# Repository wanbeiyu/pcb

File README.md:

# PCB

## 3rd_party libraries

<table>
<tr><th>Part Number</th><th>Download Link</th></tr>
<tr><td>2171790001</td><td>

[ul_2171790001.zip](https://app.ultralibrarian.com/details/b6ea985d-a10c-11eb-9033-0a34d6323d74/Molex-Connector-Corporation/2171790001)

<dl>
<dt>Symbol</dt><dd>Normal View, 2171790001 1</dd>
<dt>Footprint</dt><dd>Basic View, 2171790001_MOL</dd>
<dt>Select Your CAD Format</dt><dd>3D CAD Model: STEP, KiCAD v6+</dd>
<dt>Symbol Pin Ordering</dt><dd>Sequential</dd>
<dt>Footprint Units</dt><dd>English (mil)</dd>
</dl>

フットプリントは作り直した。

</td></tr>
<tr><td>AD8403ARUZ1-REEL</td><td>

[LIB_AD8403ARUZ1-REEL.zip](https://componentsearchengine.com/part-view/AD8403ARUZ1-REEL/Analog%20Devices)

</td></tr>
<tr><td>ADG801BRTZ-REEL7</td><td>

[LIB_ADG801BRTZ-REEL7.zip](https://componentsearchengine.com/part-view/ADG801BRTZ-REEL7/Analog%20Devices)

</td></tr>
<tr><td>AWSCR-12.00CELA-C10-T3</td><td>

C33なら存在する。シンボルのプロパティから「値」「Manufacturer_Part_Number」を編集し、「データシート」「説明」「Mouser Part Number」「Mouser Price/Stock」「Arrow Part Number」「Arrow Price/Stock」の内容を削除の上、PCBA時にC10を指定する。

[LIB_AWSCR-12.00CELA-C33-T3.zip](https://componentsearchengine.com/part-view/AWSCR-12.00CELA-C33-T3/ABRACON)

</td></tr>
<tr><td>DS4424N+T&R</td><td>

[LIB_DS4424N+T&R.zip](https://componentsearchengine.com/part-view/DS4424N%2BT%26R/Analog%20Devices)

</td></tr>
<tr><td>MCP659-E_ML</td><td>

[LIB_MCP659-E_ML.zip](https://componentsearchengine.com/part-view/MCP659-E%2FML/Microchip)

</td></tr>
<tr><td>NCP167AMX330TBG</td><td>

[ul_NCP167AMX330TBG.zip](https://app.ultralibrarian.com/details/5d94e4bf-e68c-11ea-b55a-0a34d6323d74/onsemi/NCP167AMX330TBG)

<dl>
<dt>Symbol</dt><dd>Normal View, NCP167AMX330TBG 1</dd>
<dt>Footprint</dt><dd>Basic View, XDFN4_1X1_711AJ_ONS</dd>
<dt>Select Your CAD Format</dt><dd>KiCAD v6+</dd>
<dt>Symbol Pin Ordering</dt><dd>Sequential</dd>
<dt>Footprint Units</dt><dd>English (mil)</dd>
</dl>
</td></tr>
<tr><td>SK6805-EC15</td><td>

[LIB_SK6805-EC15.zip](https://componentsearchengine.com/part-view/SK6805-EC15/Shenzhen%20Normand%20Electronic)

</td></tr>
<tr><td>TC42X-2-102E</td><td>

[LIB_TC42X-2-102E.zip](https://componentsearchengine.com/part-view/TC42X-2-102E/Bourns)

</td></tr>
<tr><td>W25Q16JVUXIQ</td><td>

[LIB_W25Q16JVUXIQ.zip](https://componentsearchengine.com/part-view/W25Q16JVUXIQ/Winbond)

</td></tr>
<tr><td>XCL103D503CR-G</td><td>

[LIB_XCL103D503CR-G.zip](https://componentsearchengine.com/part-view/XCL103D503CR-G/Torex)

</td></tr>
</table>

## 部品選定メモ

### 電源

New 3DS LLには5V以上の電源を引き出せるTPはない（電源接続時4.38V、バッテリー駆動時3.92V、消耗時は3.1V程度まで低下）。5Vに昇圧→3.3Vに降圧する。

特にコイル一体型のICが実装面積が小さくなる。XCL103のI<sub>LIM</sub>で十分と判断した。

<table>
<tr>
<th>品番</th>
<th>詳細</th>
</tr>
<tr>
<td>XCL103D503CR-G</td>
<td>

- PWM/PFM自動切替制御
- Complete Output Disconnect
- Output Voltage: 5.0V
- I<sub>LIM</sub>: 1.3A

</td>
</tr>
<tr>
<td>XCL105A501H2-G</td>
<td>

- PWM/PFM制御
- Complete Output Disconnect
  - A・Dから選択で、Aしか在庫がない<br>https://www.digikey.jp/short/0qb0394h<br>https://mou.sr/4bJGSOZ
- Output Voltage: 5.0V
- I<sub>LIM</sub>: 2.42A

</td>
</tr>
</table>

以前はRaspberry Pi Debug Probeを参考に[AP2112K-3.3TRG1](https://www.digikey.jp/ja/products/detail/diodes-incorporated/AP2112K-3-3TRG1/4470746)を使用していた。

| 機能                     | 値         |
| ------------------------ | ---------- |
| 出力構成                 | ポジティブ |
| 出力タイプ               | 固定       |
| 電圧 - 出力（最小/固定） | 3.3V       |
| 電流 - 出力              | 600mA      |

600mA以上出ていればどれでもよさそうだ。[NCP167AMX330TBG](https://www.digikey.jp/ja/products/detail/onsemi/NCP167AMX330TBG/9169759)が十分小さい。

### 発振回路

[AEL X12M000000S096](https://abracon.com/datasheets/AEL-Crystals/PN/X12M000000S096.pdf)が元の水晶[^1]。

[^1]: https://forums.raspberrypi.com/viewtopic.php?t=349741

- 12MHz
- ESR：50Ωに寄せる
- 内蔵コンデンサ
- セラミックタイプ

[検索結果](https://www.digikey.jp/short/p5qp35qr)

Operating Temperature（`CELA`は85度まで、`CELB`は125度まで）、静電容量（33pF／10pF）を選択する。以前の設計では10pFを用いたので、今回も10pF+1kΩ抵抗で使用する。

[AWSCR-12.00CELA-C10-T3](https://www.digikey.jp/short/t2mnvzrp)

## フルカラーLED

いわゆるNeoPixel、WS2812BとSK6812（12mA：たぶんより明るい）/SK6805（5mA）は同じものらしい[^2]。前者がオリジナル、後者がクローン。

[^2]: https://romly.com/blog/neopixel_variation/

SK6805-EC15が1.5mm角。

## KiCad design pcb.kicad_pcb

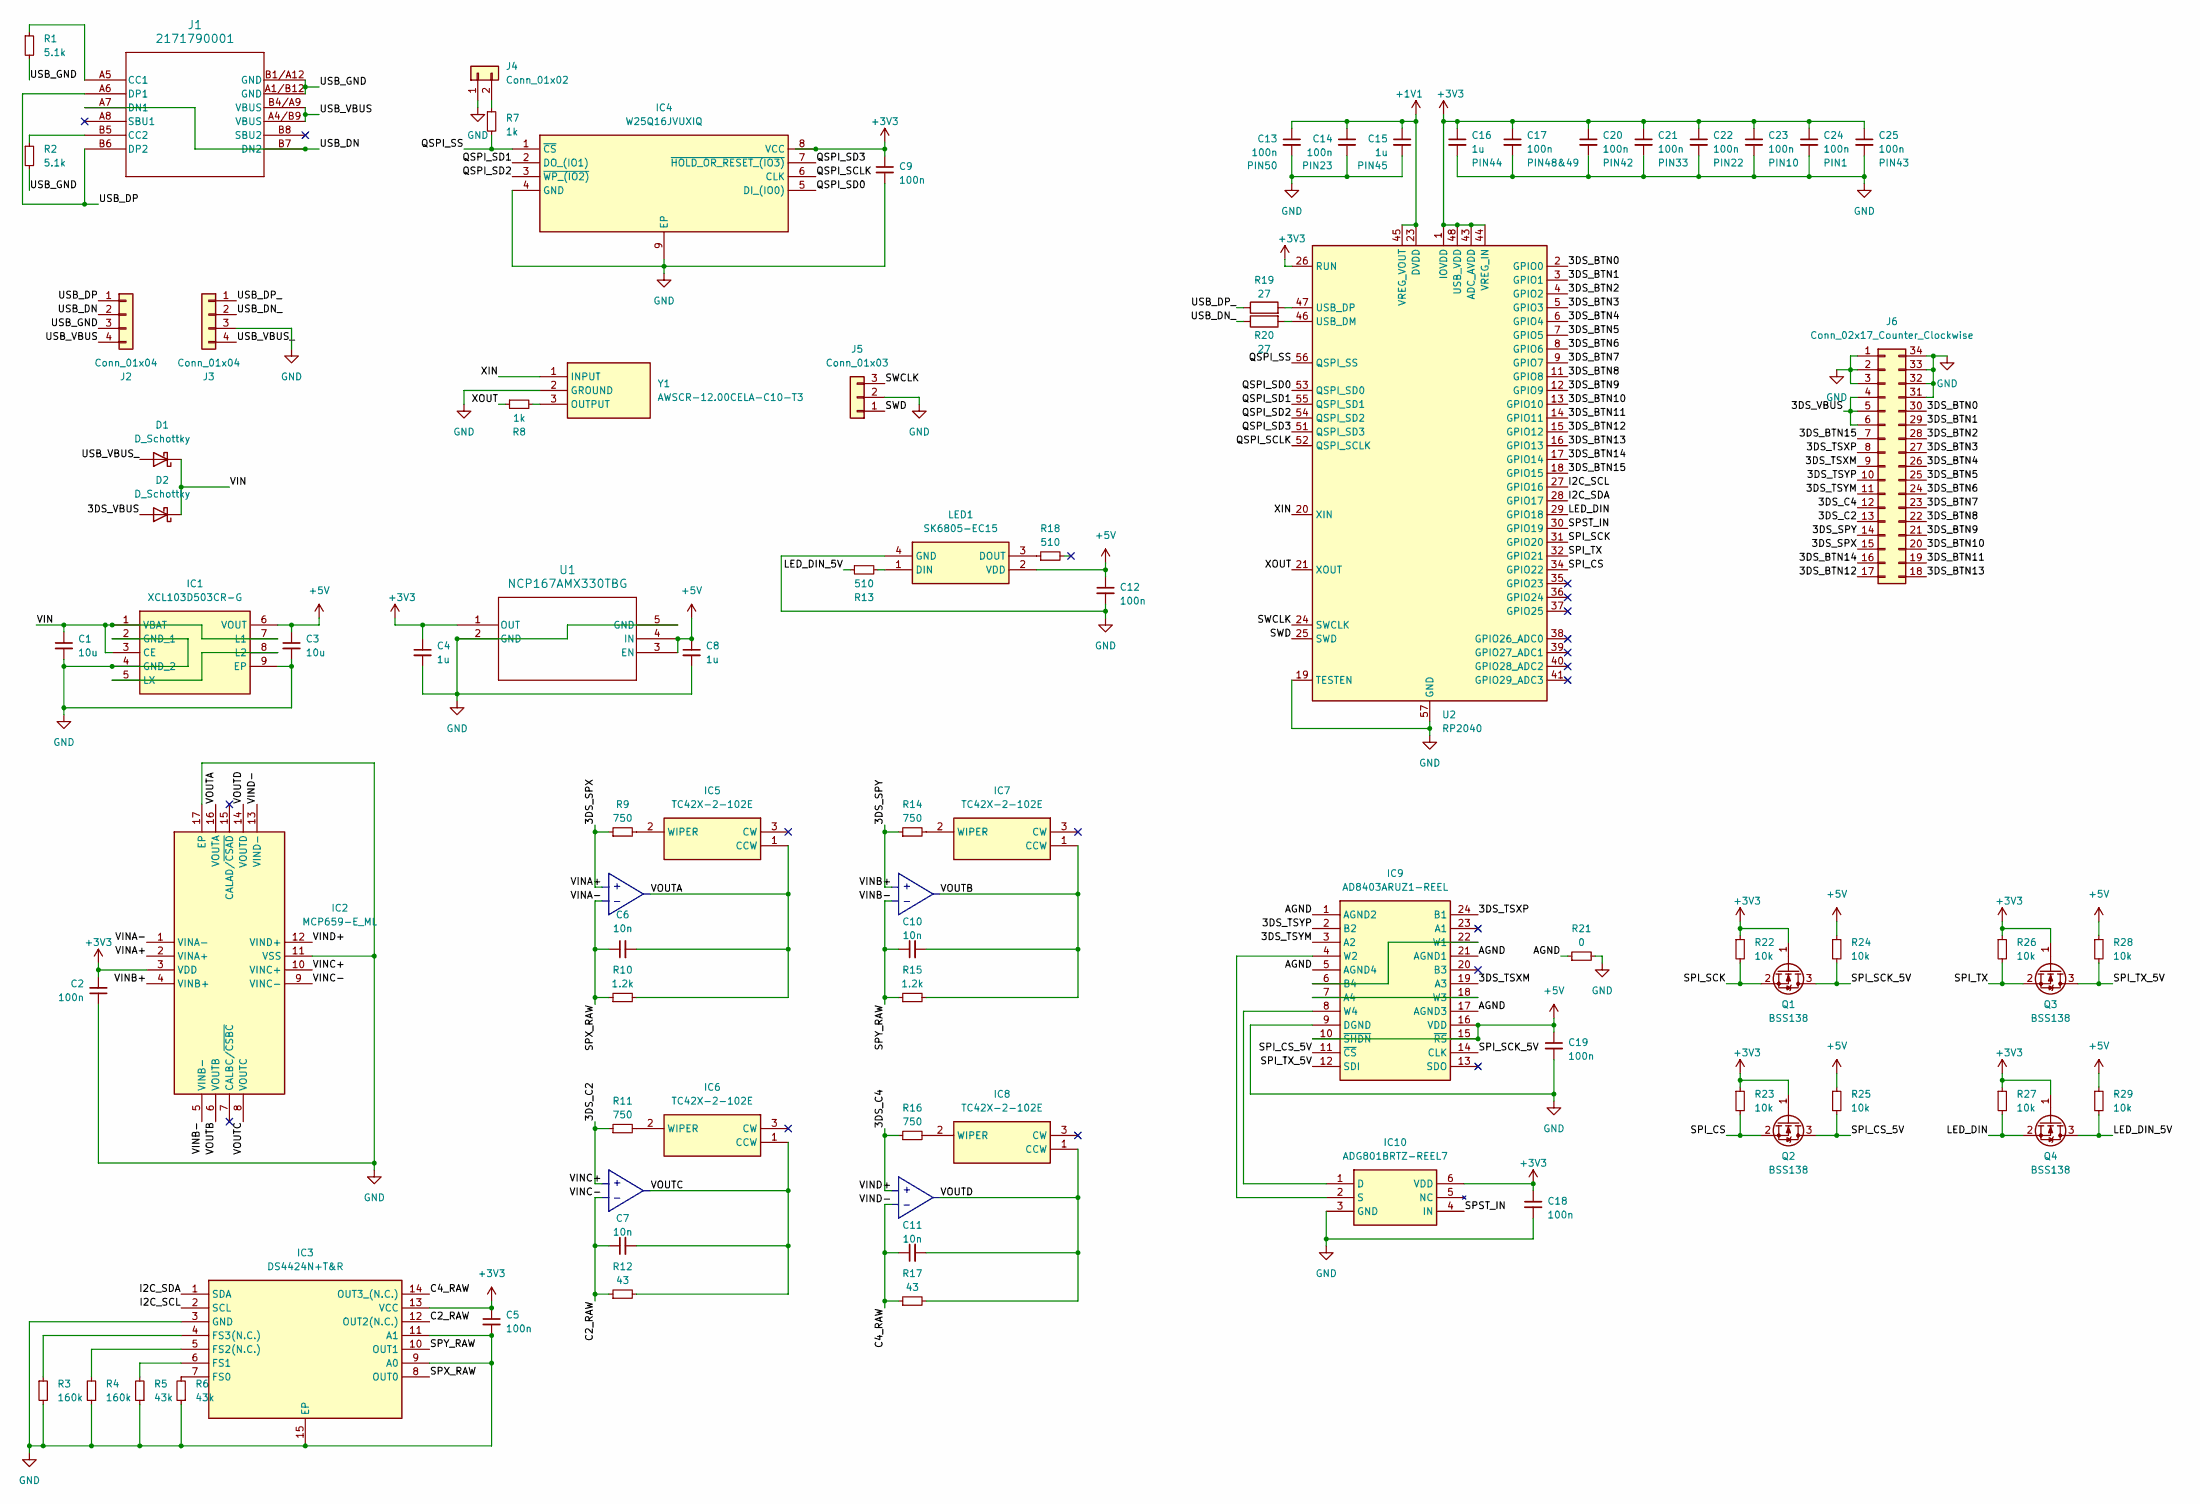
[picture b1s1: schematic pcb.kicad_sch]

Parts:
C1, C3: 10u; C_0603_1608Metric; Part TMK107BBJ106MA-T; LCSC C386081
C2, C5, C9, C12, C13, C14, C17, C18, C19, C20, C21, C22, C23, C24, C25: 100n; C_0201_0603Metric
C4, C8, C15, C16: 1u; C_0201_0603Metric
C6, C7, C10, C11: 10n; C_0201_0603Metric
D1, D2: D_Schottky; D_SOD-523
IC1: XCL103D503CR-G; XCL103D503CRG; Manufacturer_Part_Number XCL103D503CR-G; Mouser Part Number 865-XCL103D503CR-G
IC2: MCP659-E_ML; QFN65P400X400X100-17N-D; Manufacturer_Part_Number MCP659-E/ML
IC3: DS4424N+T&R; SON40P300X300X80-15N; Manufacturer_Part_Number DS4424N+T&R; Mouser Part Number 700-DS4424NT&R
IC4: W25Q16JVUXIQ; SON50P300X200X60-9N; Manufacturer_Part_Number W25Q16JVUXIQ
IC5, IC6, IC7, IC8: TC42X-2-102E; TC42X2102E; Manufacturer_Part_Number TC42X-2-102E; Mouser Part Number 652-TC42X-2-102E
IC9: AD8403ARUZ1-REEL; SOP65P640X120-24N; Manufacturer_Part_Number AD8403ARUZ1-REEL; Mouser Part Number 584-AD8403ARUZ1-R
IC10: ADG801BRTZ-REEL7; SOT95P280X145-6N; Manufacturer_Part_Number ADG801BRTZ-REEL7; Mouser Part Number 584-ADG801BRTZ-R7
J1: 2171790001
J2, J3: Conn_01x04; PinHeader_1x04_P1.27mm_Vertical
J4: Conn_01x02; PinHeader_1x02_P1.27mm_Vertical
J5: Conn_01x03; PinHeader_1x03_P1.27mm_Vertical
J6: Conn_02x17_Counter_Clockwise; 5055503020
LED1: SK6805-EC15; SK6805EC15; Manufacturer_Part_Number SK6805-EC15
Q1, Q2, Q3, Q4: BSS138; SOT-23
R1, R2: 5.1k; R_0201_0603Metric
R3, R4: 160k; R_0201_0603Metric
R5, R6: 43k; R_0201_0603Metric
R7, R8: 1k; R_0201_0603Metric
R9, R11, R14, R16: 750; R_0201_0603Metric
R10, R15: 1.2k; R_0201_0603Metric
R12, R17: 43; R_0201_0603Metric
R13, R18: 510; R_0201_0603Metric
R19, R20: 27; R_0201_0603Metric
R21: 0; R_0201_0603Metric
R22, R23, R24, R25, R26, R27, R28, R29: 10k; R_0201_0603Metric
U1: NCP167AMX330TBG; XDFN4_1X1_711AJ_ONS
U2: RP2040; QFN-56-1EP_7x7mm_P0.4mm_EP3.2x3.2mm
Y1: AWSCR-12.00CELA-C10-T3; AWSCR1200CELAC33T3; Manufacturer_Part_Number AWSCR-12.00CELA-C10-T3

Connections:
+1V1: C13.1, C14.1, C15.1, U2.23 (DVDD), U2.45 (VREG_VOUT), U2.50 (DVDD)
+3V3: C2.2, C4.1, C5.1, C9.1, C16.1, C17.1, C18.1, C20.1, C21.1, C22.1, C23.1, C24.1, C25.1, IC2.3 (VDD), IC3.13 (VCC), IC4.8 (VCC), IC10.6 (VDD), Q1.1 (G), Q2.1 (G), Q3.1 (G), Q4.1 (G), R22.1, R23.1, R26.1, R27.1, U1.1 (OUT), U2.1 (IOVDD), U2.10 (IOVDD), U2.22 (IOVDD), U2.26 (RUN), U2.33 (IOVDD), U2.42 (IOVDD), U2.43 (ADC_AVDD), U2.44 (VREG_IN), U2.48 (USB_VDD), U2.49 (IOVDD)
+5V: C3.1, C8.1, C12.1, C19.1, IC1.6 (VOUT), IC9.10 (~SHDN), IC9.15 (~RS), IC9.16 (VDD), LED1.2 (VDD), R24.1, R25.1, R28.1, R29.1, U1.3 (EN), U1.4 (IN)
/3DS_BTN0: J6.30, U2.2 (GPIO0)
/3DS_BTN1: J6.29, U2.3 (GPIO1)
/3DS_BTN2: J6.28, U2.4 (GPIO2)
/3DS_BTN3: J6.27, U2.5 (GPIO3)
/3DS_BTN4: J6.26, U2.6 (GPIO4)
/3DS_BTN5: J6.25, U2.7 (GPIO5)
/3DS_BTN6: J6.24, U2.8 (GPIO6)
/3DS_BTN7: J6.23, U2.9 (GPIO7)
/3DS_BTN8: J6.22, U2.11 (GPIO8)
/3DS_BTN9: J6.21, U2.12 (GPIO9)
/3DS_BTN10: J6.20, U2.13 (GPIO10)
/3DS_BTN11: J6.19, U2.14 (GPIO11)
/3DS_BTN12: J6.17, U2.15 (GPIO12)
/3DS_BTN13: J6.18, U2.16 (GPIO13)
/3DS_BTN14: J6.16, U2.17 (GPIO14)
/3DS_BTN15: J6.7, U2.18 (GPIO15)
/3DS_C2: IC2.10 (VINC+), J6.13, R11.1
/3DS_C4: IC2.12 (VIND+), J6.12, R16.1
/3DS_SPX: IC2.2 (VINA+), J6.15, R9.1
/3DS_SPY: IC2.4 (VINB+), J6.14, R14.1
/3DS_TSXM: IC9.19 (A3), J6.9
/3DS_TSXP: IC9.24 (B1), J6.8
/3DS_TSYM: IC9.3 (A2), J6.11
/3DS_TSYP: IC9.2 (B2), J6.10
/3DS_VBUS: D2.2 (A), J6.4, J6.5, J6.6
/AGND: IC9.1 (AGND2), IC9.5 (AGND4), IC9.17 (AGND3), IC9.21 (AGND1), R21.1
/C2_RAW: C7.1, IC2.9 (VINC-), IC3.12 (OUT2(N.C.)), R12.1
/C4_RAW: C11.1, IC2.13 (VIND-), IC3.14 (OUT3_(N.C.)), R17.1
/I2C_SCL: IC3.2 (SCL), U2.27 (GPIO16)
/I2C_SDA: IC3.1 (SDA), U2.28 (GPIO17)
/LED_DIN: Q4.2 (S), R27.2, U2.29 (GPIO18)
/LED_DIN_5V: Q4.3 (D), R13.1, R29.2
/QSPI_SCLK: IC4.6 (CLK), U2.52 (QSPI_SCLK)
/QSPI_SD0: IC4.5 (DI_(IO0)), U2.53 (QSPI_SD0)
/QSPI_SD1: IC4.2 (DO_(IO1)), U2.55 (QSPI_SD1)
/QSPI_SD2: IC4.3 (~WP_(IO2)), U2.54 (QSPI_SD2)
/QSPI_SD3: IC4.7 (~HOLD_OR_RESET_(IO3)), U2.51 (QSPI_SD3)
/QSPI_SS: IC4.1 (~CS), R7.2, U2.56 (QSPI_SS)
/SPI_CS: Q2.2 (S), R23.2, U2.34 (GPIO22)
/SPI_CS_5V: IC9.11 (~CS), Q2.3 (D), R25.2
/SPI_SCK: Q1.2 (S), R22.2, U2.31 (GPIO20)
/SPI_SCK_5V: IC9.14 (CLK), Q1.3 (D), R24.2
/SPI_TX: Q3.2 (S), R26.2, U2.32 (GPIO21)
/SPI_TX_5V: IC9.12 (SDI), Q3.3 (D), R28.2
/SPST_IN: IC10.4 (IN), U2.30 (GPIO19)
/SPX_RAW: C6.1, IC2.1 (VINA-), IC3.8 (OUT0), R10.1
/SPY_RAW: C10.1, IC2.5 (VINB-), IC3.10 (OUT1), R15.1
/SWCLK: J5.3, U2.24 (SWCLK)
/SWD: J5.1, U2.25 (SWD)
/USB_DN: J1.A7 (DN1), J1.B7 (DN2), J2.2
/USB_DN_: J3.2, R20.1
/USB_DP: J1.A6 (DP1), J1.B6 (DP2), J2.1
/USB_DP_: J3.1, R19.1
/USB_GND: J1.A1/B12 (GND), J1.B1/A12 (GND), J2.3, R1.2, R2.2
/USB_VBUS: J1.A4/B9 (VBUS), J1.B4/A9 (VBUS), J2.4
/USB_VBUS_: D1.2 (A), J3.4
/VIN: C1.1, D1.1 (K), D2.1 (K), IC1.1 (VBAT), IC1.3 (CE), IC1.7 (L1)
/VOUTA: C6.2, IC2.16 (VOUTA), IC5.1 (CCW), R10.2
/VOUTB: C10.2, IC2.6 (VOUTB), IC7.1 (CCW), R15.2
/VOUTC: C7.2, IC2.8 (VOUTC), IC6.1 (CCW), R12.2
/VOUTD: C11.2, IC2.14 (VOUTD), IC8.1 (CCW), R17.2
/XIN: U2.20 (XIN), Y1.1 (INPUT)
/XOUT: R8.1, U2.21 (XOUT)
GND: C1.2, C2.1, C3.2, C4.2, C5.2, C8.2, C9.2, C12.2, C13.2, C14.2, C15.2, C16.2, C17.2, C18.2, C19.2, C20.2, C21.2, C22.2, C23.2, C24.2, C25.2, IC1.2 (GND_1), IC1.4 (GND_2), IC1.9 (EP), IC2.11 (VSS), IC2.17 (EP), IC3.3 (GND), IC3.9 (A0), IC3.11 (A1), IC3.15 (EP), IC4.4 (GND), IC4.9 (EP), IC9.9 (DGND), IC10.3 (GND), J3.3, J4.1, J5.2, J6.1, J6.2, J6.3, J6.31, J6.32, J6.33, J6.34, LED1.4 (GND), R3.2, R4.1, R5.1, R6.1, R21.2, U1.2 (GND), U1.5 (GND), U2.19 (TESTEN), U2.57 (GND), Y1.2 (GROUND)
unnamed: IC1.5 (LX), IC1.8 (L2)
unnamed: IC3.7 (FS0), R6.2
unnamed: IC3.6 (FS1), R5.2
unnamed: IC3.5 (FS2(N.C.)), R4.2
unnamed: IC3.4 (FS3(N.C.)), R3.1
unnamed: IC5.2 (WIPER), R9.2
unnamed: IC6.2 (WIPER), R11.2
unnamed: IC7.2 (WIPER), R14.2
unnamed: IC8.2 (WIPER), R16.2
unnamed: IC9.7 (A4), IC9.18 (W3)
unnamed: IC9.6 (B4), IC9.22 (W1)
unnamed: IC9.8 (W4), IC10.1 (D)
unnamed: IC9.4 (W2), IC10.2 (S)
unnamed: J1.A5 (CC1), R1.1
unnamed: J1.B5 (CC2), R2.1
unnamed: J4.2, R7.1
unnamed: LED1.1 (DIN), R13.2
unnamed: LED1.3 (DOUT), R18.1
unnamed: R20.2, U2.46 (USB_DM)
unnamed: R19.2, U2.47 (USB_DP)
unnamed: R8.2, Y1.3 (OUTPUT)

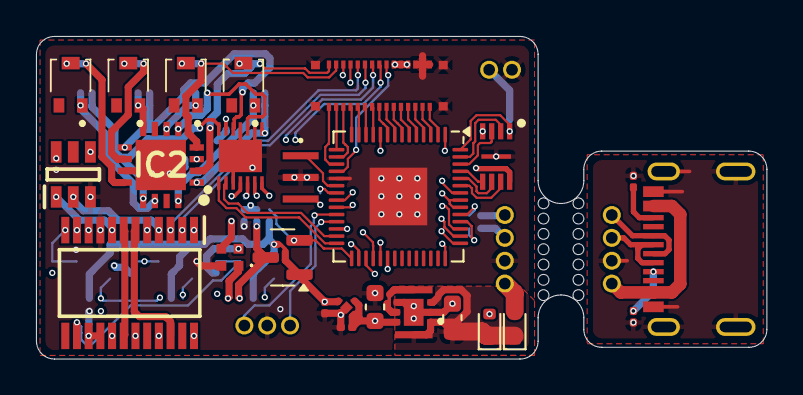
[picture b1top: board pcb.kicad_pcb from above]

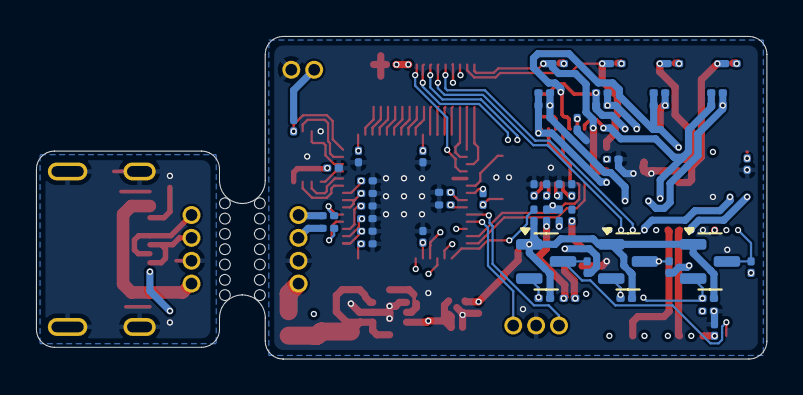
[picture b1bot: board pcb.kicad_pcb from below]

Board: 4 copper layers, 40.6 x 17.9 mm, 80 parts (51 on the bottom side), 88 nets.

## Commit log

2024-05-20 Add files
2024-05-20 Add .gitignore
2024-05-20 Add library
2024-06-09 Update gitignore
